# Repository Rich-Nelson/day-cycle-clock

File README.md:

# day-cycle-clock

This repository contains the mechanical and electrical CAD for the Day Cycle Clock.  The code can be found in this repo https://github.com/Rich-Nelson/day-cycle-clock-code

Links to the build video and blog post coming soon.

## CAD
Contains the mechanical models.  In the root directoy there is a .STEP and .SLDASM of the full assembly

- **STL** Has all of the printable files for the project
- **SLDPRT** Contains the individual component models and sub assemblies
- **SLDDRW** Contaisn the 2-D dimensioned drawings for some of the fabricated components, mainly the wooden enclosure
- **Backlight Bracket** 3 versions of the backlight screen assembly were made depending on which you want to use.
    - **v1** Backlight assembly with through hole 5mm LEDs
    - **v2** Backlight assembly with SMD LEDs on perf board
    - **v3** Backlight assembly with custom PCB (found int he PCB folder)

## PCB
Contains the KiCAD PCB files and Gerbers.

**Note** I may need to update some customer libraries into this repo so that the KiCAD project will load properly on other computers.  But for now the gerbers are available to make your own boards.

## Graphics
Contains the vector outlines used for the 3 cutout layers.

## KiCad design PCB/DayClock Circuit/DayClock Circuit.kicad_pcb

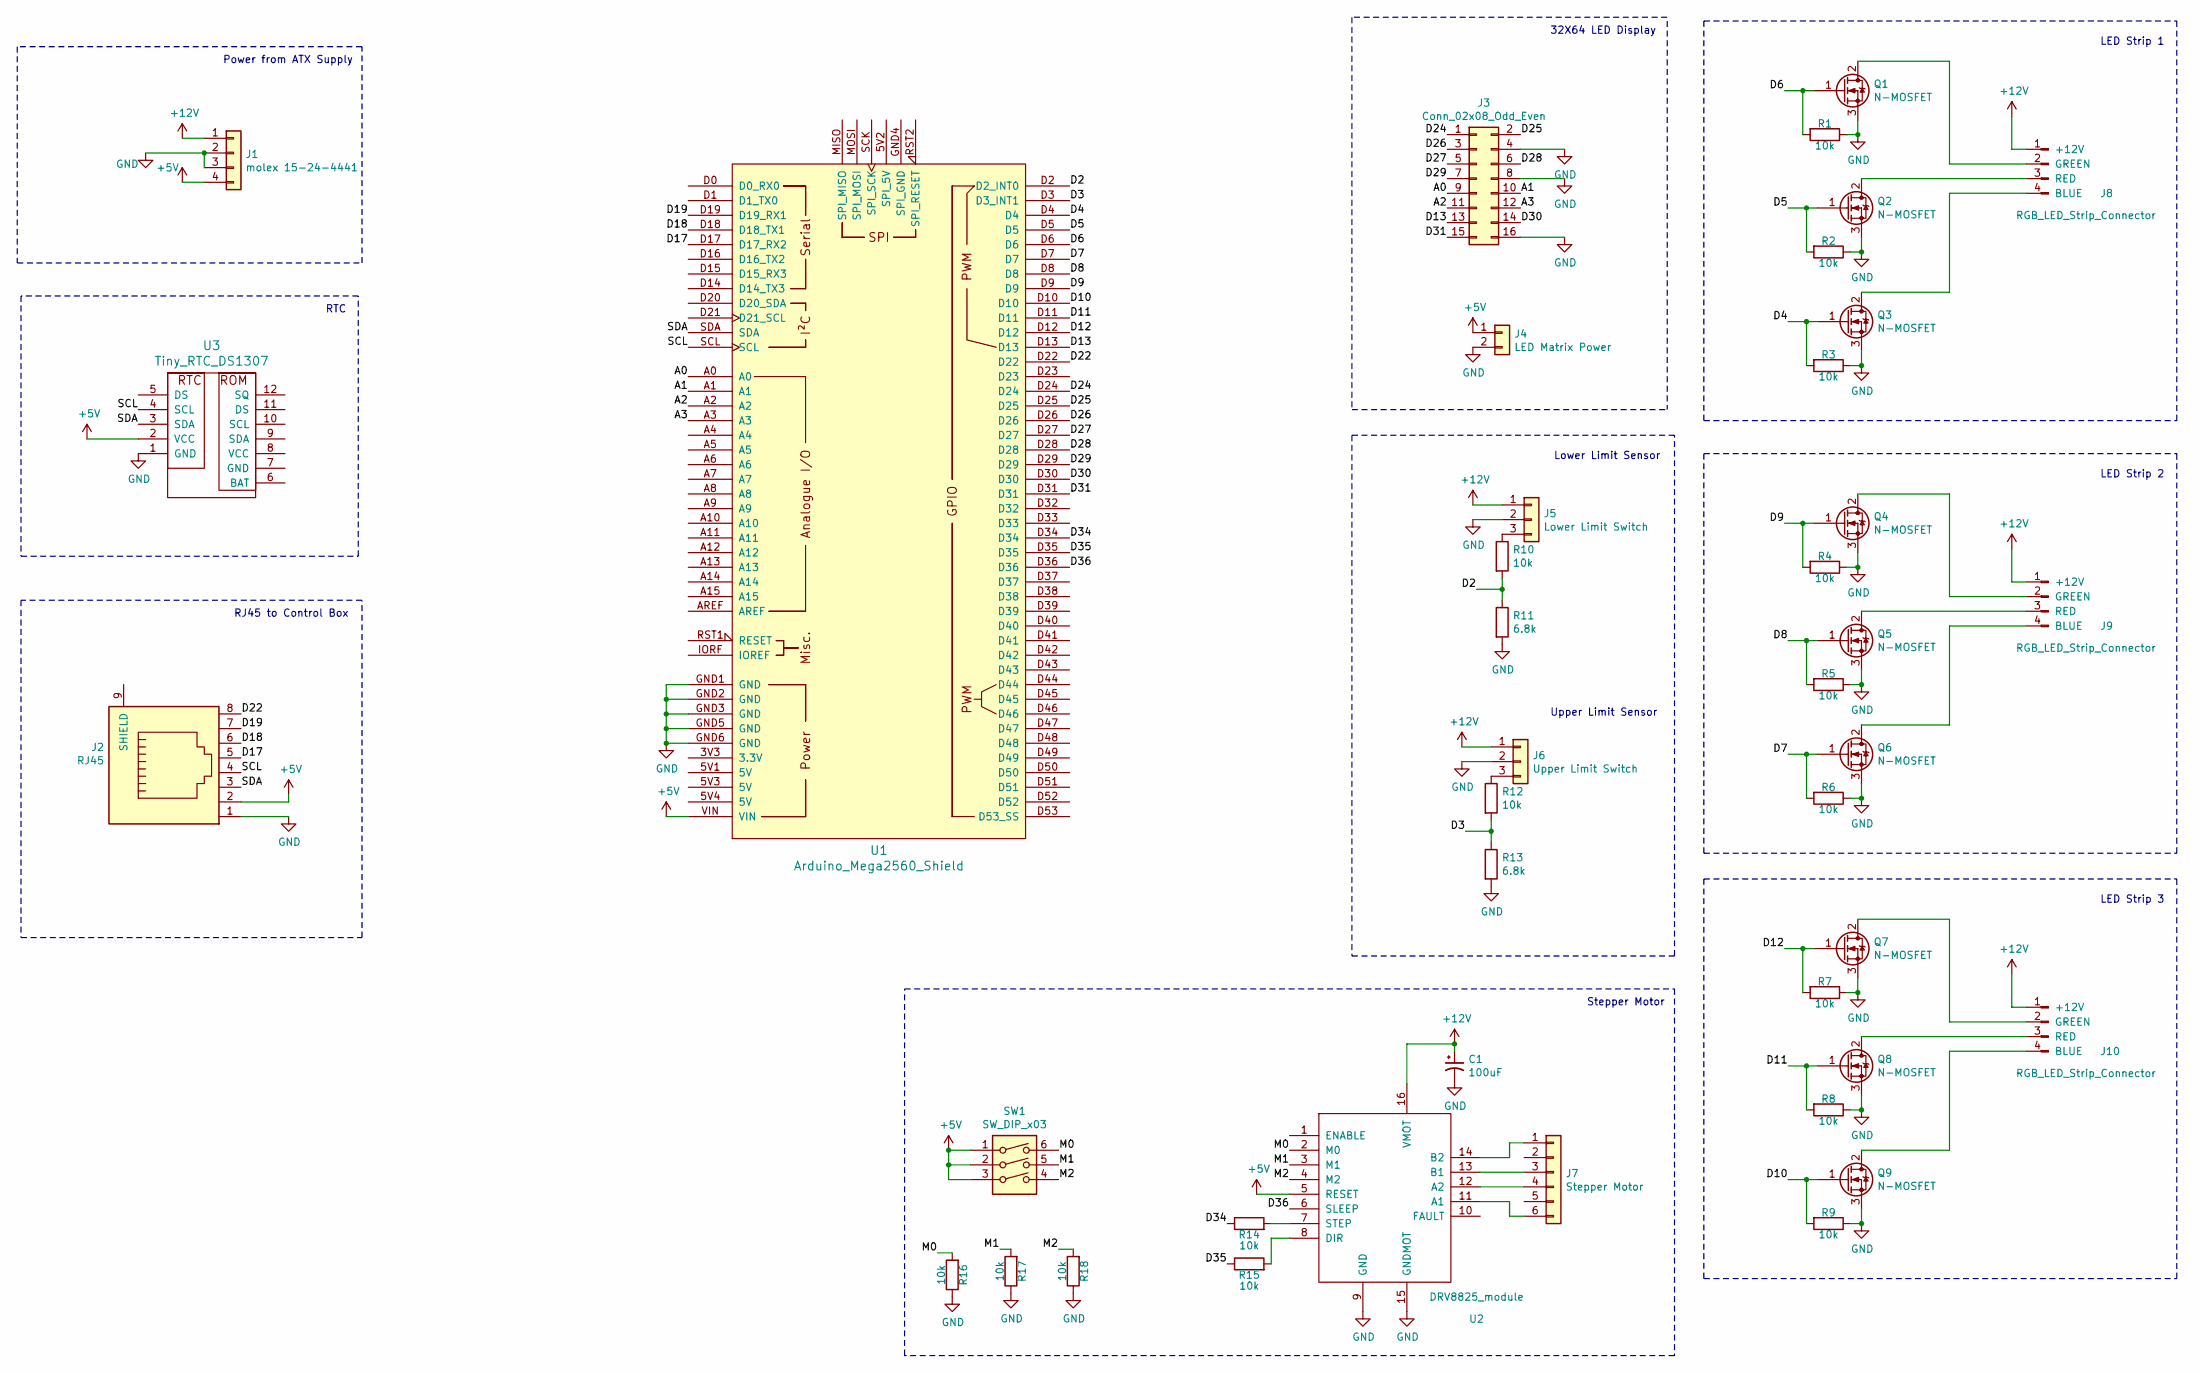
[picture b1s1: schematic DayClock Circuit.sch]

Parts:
C1: 100uF; CP_Radial_D6.3mm_P2.50mm
J1: molex 15-24-4441; Molex_15-24-4449_ATX_Power_Supply_Connector
J2: RJ45; RJ45_Amphenol_RJHSE538X
J3: Conn_02x08_Odd_Even; 3M_Header_2x8_Keyed
J4: LED Matrix Power; TerminalBlock_Altech_AK300-2_P5.00mm
J5: Lower Limit Switch; JST_XH_B03B-XH-A_1x03_P2.50mm_Vertical
J6: Upper Limit Switch; JST_XH_B03B-XH-A_1x03_P2.50mm_Vertical
J7: Stepper Motor; JST_XH_B06B-XH-A_1x06_P2.50mm_Vertical
J8, J9, J10: RGB_LED_Strip_Connector; JST_XH_B04B-XH-A_1x04_P2.50mm_Vertical
Q1, Q2, Q3, Q4, Q5, Q6, Q7, Q8, Q9: N-MOSFET; TO-251_IPAK_Vertical
R1, R2, R3, R4, R5, R6, R7, R8, R9, R10, R12, R14, R15, R16, R17, R18: 10k; R_0805_2012Metric_Pad1.15x1.50mm_HandSolder
R11, R13: 6.8k; R_0805_2012Metric_Pad1.15x1.50mm_HandSolder
SW1: SW_DIP_x03; SW_DIP_SPSTx03_Slide_6.7x9.18mm_W7.62mm_P2.54mm_LowProfile
U1: Arduino_Mega2560_Shield; Arduino_Mega2560_Shield_No_Serial_Header
U2: DRV8825_module; DRV8825_board
U3: Tiny_RTC_DS1307; TinyRTC-one-mounting-hole

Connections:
+5V: J1.4, J2.2, J4.1, SW1.1, SW1.2, SW1.3, U1.VIN, U2.5 (RESET), U3.2 (VCC)
+12V: C1.1, J1.1, J5.1, J6.1, J8.1 (+12V), J9.1 (+12V), J10.1 (+12V), U2.16 (VMOT); also elsewhere on the board
/5V3: U1.5V3 (5V); also elsewhere on the board
/A0: J3.9, U1.A0
/A1: J3.10, U1.A1
/A2: J3.11, U1.A2
/A3: J3.12, U1.A3
/D0: U1.D0 (D0_RX0); also elsewhere on the board
/D1: U1.D1 (D1_TX0); also elsewhere on the board
/D2: R10.2, R11.1, U1.D2 (D2_INT0)
/D3: R12.2, R13.1, U1.D3 (D3_INT1)
/D4: Q3.1 (G), R3.2, U1.D4
/D5: Q2.1 (G), R2.2, U1.D5
/D6: Q1.1 (G), R1.2, U1.D6
/D7: Q6.1 (G), R6.2, U1.D7
/D8: Q5.1 (G), R5.2, U1.D8
/D9: Q4.1 (G), R4.2, U1.D9
/D10: Q9.1 (G), R9.2, U1.D10
/D11: Q8.1 (G), R8.2, U1.D11
/D12: Q7.1 (G), R7.2, U1.D12
/D13: J3.13, U1.D13
/D14: U1.D14 (D14_TX3); also elsewhere on the board
/D15: U1.D15 (D15_RX3); also elsewhere on the board
/D16: U1.D16 (D16_TX2); also elsewhere on the board
/D17: J2.5, U1.D17 (D17_RX2)
/D18: J2.6, U1.D18 (D18_TX1)
/D19: J2.7, U1.D19 (D19_RX1)
/D20: U1.D20 (D20_SDA); also elsewhere on the board
/D21: U1.D21 (D21_SCL); also elsewhere on the board
/D22: J2.8, U1.D22
/D24: J3.1, U1.D24
/D25: J3.2, U1.D25
/D26: J3.3, U1.D26
/D27: J3.5, U1.D27
/D28: J3.6, U1.D28
/D29: J3.7, U1.D29
/D30: J3.14, U1.D30
/D31: J3.15, U1.D31
/D34: R14.1, U1.D34
/D35: R15.1, U1.D35
/D36: U1.D36, U2.6 (SLEEP)
/M0: R16.2, SW1.6, U2.2 (M0)
/M1: R17.2, SW1.5, U2.3 (M1)
/M2: R18.2, SW1.4, U2.4 (M2)
/SCL: J2.4, U1.SCL, U3.4 (SCL)
/SDA: J2.3, U1.SDA, U3.3 (SDA)
GND: C1.2, J1.2, J1.3, J2.1, J3.4, J3.8, J3.16, J4.2, J5.2, J6.2, Q1.3 (S), Q2.3 (S), Q3.3 (S), Q4.3 (S), Q5.3 (S), Q6.3 (S), Q7.3 (S), Q8.3 (S), Q9.3 (S), R1.1, R2.1, R3.1, R4.1, R5.1, R6.1, R7.1, R8.1, R9.1, R11.2, R13.2, R16.1, R17.1, R18.1, U1.GND1 (GND), U1.GND2 (GND), U1.GND3 (GND), U1.GND5 (GND), U1.GND6 (GND), U2.9 (GND), U2.15 (GNDMOT), U3.1 (GND); also elsewhere on the board
unnamed: J5.3, R10.1
unnamed: J6.3, R12.1
unnamed: J7.1, U2.14 (B2)
unnamed: J7.3, U2.13 (B1)
unnamed: J7.4, U2.12 (A2)
unnamed: J7.6, U2.11 (A1)
unnamed: J8.2 (GREEN), Q1.2 (D)
unnamed: J8.3 (RED), Q2.2 (D)
unnamed: J8.4 (BLUE), Q3.2 (D)
unnamed: J9.2 (GREEN), Q4.2 (D)
unnamed: J9.3 (RED), Q5.2 (D)
unnamed: J9.4 (BLUE), Q6.2 (D)
unnamed: J10.2 (GREEN), Q7.2 (D)
unnamed: J10.3 (RED), Q8.2 (D)
unnamed: J10.4 (BLUE), Q9.2 (D)
unnamed: R14.2, U2.7 (STEP)
unnamed: R15.2, U2.8 (DIR)

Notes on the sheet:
LED Strip 1
LED Strip 2
LED Strip 3
32X64 LED Display
RTC
Power from ATX Supply
Upper Limit Sensor
Lower Limit Sensor
Stepper Motor
RJ45 to Control Box

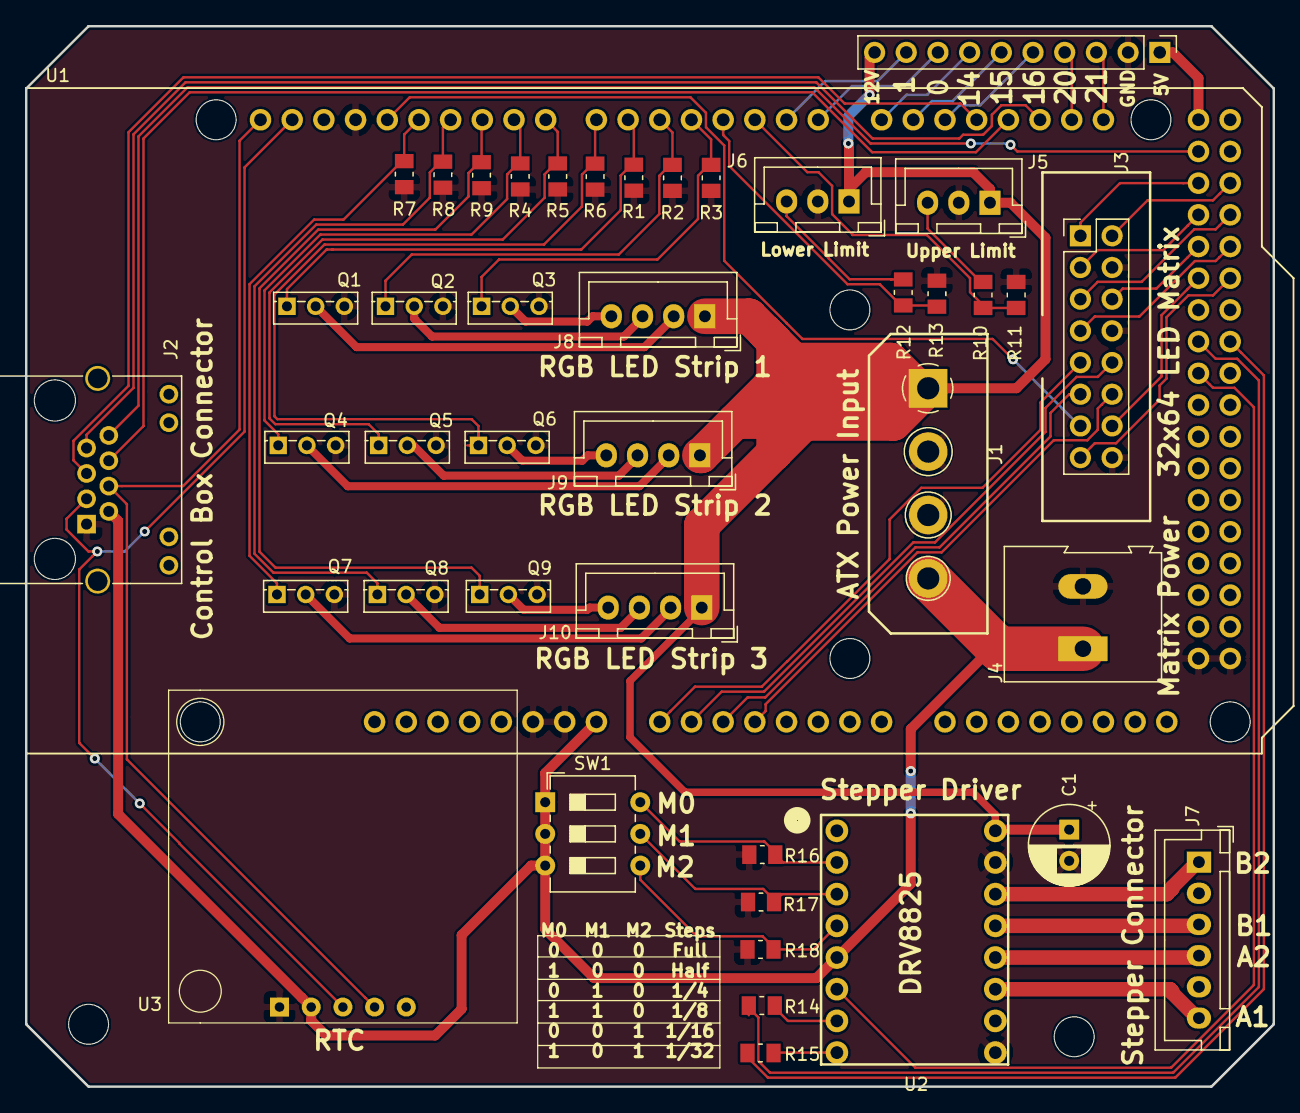
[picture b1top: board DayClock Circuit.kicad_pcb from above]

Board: 2 copper layers, 100.0 x 85.0 mm, 43 parts (0 on the bottom side), 64 nets.

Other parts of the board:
J11: Breakout Pins; PinHeader_1x10_P2.54mm_Vertical

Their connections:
+12V: J11.10; also elsewhere on the board
/5V3: J11.1; also elsewhere on the board
/D0: J11.8; also elsewhere on the board
/D1: J11.9; also elsewhere on the board
/D14: J11.7; also elsewhere on the board
/D15: J11.6; also elsewhere on the board
/D16: J11.5; also elsewhere on the board
/D20: J11.4; also elsewhere on the board
/D21: J11.3; also elsewhere on the board
GND: J11.2; also elsewhere on the board

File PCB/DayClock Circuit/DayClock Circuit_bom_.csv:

Component,Description,Part,References,Value,Footprint,Quantity Per PCB,Datasheet
1,Polarised capacitor,CP1_Small,C1,100uF,CP_Radial_D6.3mm_P2.50mm,1,
2,"Generic connector, single row, 01x10, script generated (kicad-library-utils/schlib/autogen/connector/)",Conn_01x10,J11,Breakout Pins,PinHeader_1x10_P2.54mm_Vertical,1,
3,"Generic connector, double row, 02x08, odd/even pin numbering scheme (row 1 odd numbers, row 2 even numbers), script generated (kicad-library-utils/schlib/autogen/connector/)",Conn_02x08_Odd_Even,J3,Conn_02x08_Odd_Even,3M_Header_2x8_Keyed,1,
4,"Generic connector, single row, 01x02, script generated (kicad-library-utils/schlib/autogen/connector/)",Conn_01x02,J4,LED Matrix Power,TerminalBlock_Altech_AK300-2_P5.00mm,1,
5,"Generic connector, single row, 01x03, script generated (kicad-library-utils/schlib/autogen/connector/)",Conn_01x03,J5,Lower Limit Switch,JST_XH_B03B-XH-A_1x03_P2.50mm_Vertical,1,
6,,RGB_LED_Strip_Connector,J8 J9 J10,RGB_LED_Strip_Connector,JST_XH_B04B-XH-A_1x04_P2.50mm_Vertical,3,
7,RJ45 connector with shield,RJ45,J2,RJ45,RJ45_Amphenol_RJHSE538X,1,
8,"Generic connector, single row, 01x06, script generated (kicad-library-utils/schlib/autogen/connector/)",Conn_01x06,J7,Stepper Motor,JST_XH_B06B-XH-A_1x06_P2.50mm_Vertical,1,
9,"Generic connector, single row, 01x03, script generated (kicad-library-utils/schlib/autogen/connector/)",Conn_01x03,J6,Upper Limit Switch,JST_XH_B03B-XH-A_1x03_P2.50mm_Vertical,1,
10,"Generic connector, single row, 01x04, script generated (kicad-library-utils/schlib/autogen/connector/)",Conn_01x04,J1,molex 15-24-4441,Molex_15-24-4449_ATX_Power_Supply_Connector,1,
11,"0.35A Id, 240V Vds, N-Channel MOSFET, SOT-223",BSP129,Q1 Q2 Q3 Q4 Q5 Q6 Q7 Q8 Q9,N-MOSFET,TO-251_IPAK_Vertical,9,https://www.infineon.com/dgdl/Infineon-BSP129-DS-v01_42-en.p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
12,Resistor,R,R1 R2 R3 R4 R5 R6 R7 R8 R9 R10 R12 R14 R15 R16 R17 R18,10k,R_0805_2012Metric_Pad1.15x1.50mm_HandSolder,16,
13,Resistor,R,R11 R13,6.8k,R_0805_2012Metric_Pad1.15x1.50mm_HandSolder,2,
14,"3x DIP Switch, Single Pole Single Throw (SPST) switch, small symbol",SW_DIP_x03,SW1,SW_DIP_x03,SW_DIP_SPSTx03_Slide_6.7x9.18mm_W7.62mm_P2.54mm_LowProfile,1,
15,Shield for Arduino Mega 2560,Arduino_Mega2560_Shield,U1,Arduino_Mega2560_Shield,Arduino_Mega2560_Shield_No_Serial_Header,1,https://store.arduino.cc/arduino-mega-2560-rev3
16,,DRV8825_module,U2,DRV8825_module,DRV8825_board,1,
17,,Tiny_RTC_DS1307,U3,Tiny_RTC_DS1307,TinyRTC-coin-side-up,1,





Component Groups:,17
Component Count:,43
Fitted Components:,43
Number of PCBs:,1
Total components:,43
Schematic Version:,
Schematic Date:,
BoM Date:,6/3/2018 11:47:07 PM
Schematic Source:,C:\Users\Rich\Dropbox\Projects\Skyline Shadowbox Day Cycle\day-cycle-clock\PCB\DayClock Circuit\DayClock Circuit.sch
KiCad Version:,Eeschema (5.0.0-rc2-dev-352-g017154715)

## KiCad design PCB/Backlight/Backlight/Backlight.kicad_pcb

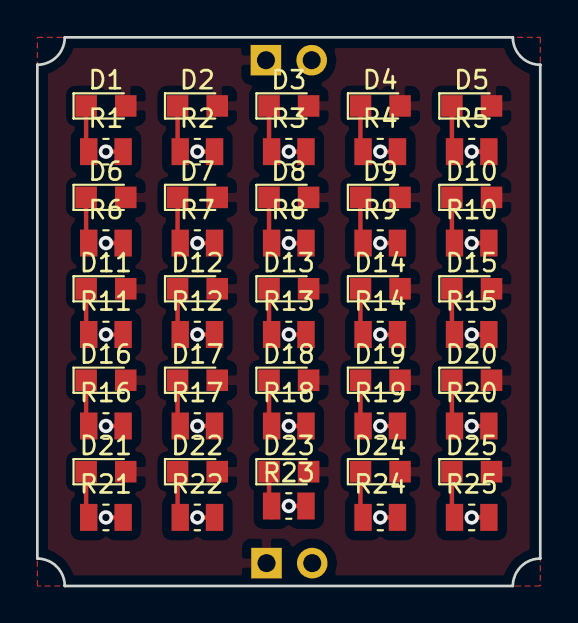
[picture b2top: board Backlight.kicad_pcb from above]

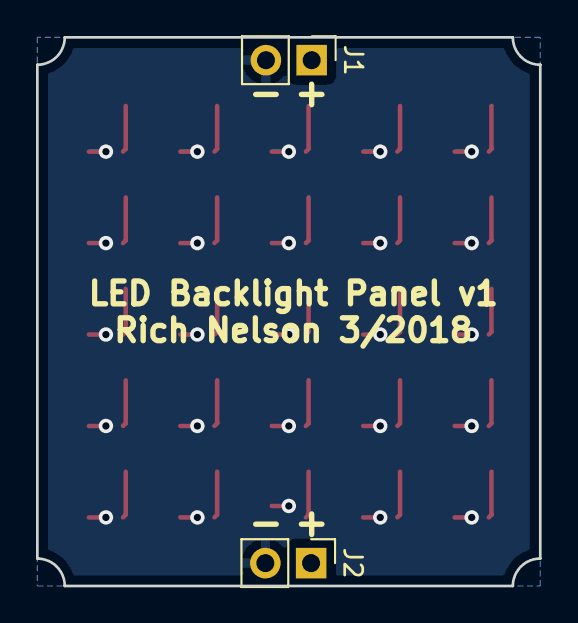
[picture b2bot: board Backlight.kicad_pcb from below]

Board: 2 copper layers, 27.9 x 30.5 mm, 52 parts (2 on the bottom side), 27 nets.

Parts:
D1, D2, D3, D4, D5, D6, D7, D8, D9, D10, D11, D12, D13, D14, D15, D16, D17, D18, D19, D20, D21, D22, D23, D24, D25: LED; LED_0805
J1, J2: Conn_01x02; PinHeader_1x02_P2.54mm_Vertical
R1, R2, R3, R4, R5, R6, R7, R8, R9, R10, R11, R12, R13, R14, R15, R16, R17, R18, R19, R20, R21, R22, R23, R24, R25: R; R_0805_2012Metric

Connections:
+5V: D1.2, D2.2, D3.2, D4.2, D5.2, D6.2, D7.2, D8.2, D9.2, D10.2, D11.2, D12.2, D13.2, D14.2, D15.2, D16.2, D17.2, D18.2, D19.2, D20.2, D21.2, D22.2, D23.2, D24.2, D25.2, J1.1, J2.1
GND: J1.2, J2.2, R1.2, R2.2, R3.2, R4.2, R5.2, R6.2, R7.2, R8.2, R9.2, R10.2, R11.2, R12.2, R13.2, R14.2, R15.2, R16.2, R17.2, R18.2, R19.2, R20.2, R21.2, R22.2, R23.2, R24.2, R25.2
unnamed: D1.1, R1.1
unnamed: D2.1, R2.1
unnamed: D3.1, R3.1
unnamed: D4.1, R4.1
unnamed: D5.1, R5.1
unnamed: D6.1, R6.1
unnamed: D7.1, R7.1
unnamed: D8.1, R8.1
unnamed: D9.1, R9.1
unnamed: D10.1, R10.1
unnamed: D11.1, R11.1
unnamed: D12.1, R12.1
unnamed: D13.1, R13.1
unnamed: D14.1, R14.1
unnamed: D15.1, R15.1
unnamed: D16.1, R16.1
unnamed: D17.1, R17.1
unnamed: D18.1, R18.1
unnamed: D19.1, R19.1
unnamed: D20.1, R20.1
unnamed: D21.1, R21.1
unnamed: D22.1, R22.1
unnamed: D23.1, R23.1
unnamed: D24.1, R24.1
unnamed: D25.1, R25.1

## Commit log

2018-05-16 Initial commit, day-cycle-clock rev 1
2018-05-19 Added support for altrnate TFT screen. there sems to be a huge numbr of 1.44 TFT screens on the marked with minor differences in dimensions and protocals.
2018-05-19 Added 2004 LCD screen connector to schematic
2018-05-22 Updated CAD for new TFT screen, and updated schamatic, adding the encoder.
2018-05-26 Updated Scheematic to inclide New RGB LED strips and i2c driver, and 32x64 matrix using an Arduino Uno
2018-05-30 Started moving components to the Arduino Mega, moved the 3 LED strips (9 PWM pins), and the 32x64 Matrix Display
2018-05-31 Added Power connecter. Moved RTC, Encoder, and 4002 LCD screen to the Arduino Mega. Lastly need to add stepper, CAT5 breakout for control box, and limit switches for the motor.
2018-06-01 Added Stepper with Driver and Proximity Sensor Limits
2018-06-01 Added resistors to steper sriver signal lines. This solved somem erratic behaviour of the stpper moving on it's own
2018-06-02 Split control box to a seperate PCB connected by a CAT5 cable. Schematic is complete, foot prints need to be finalized before layout.
2018-06-03 Added thick power traces and design rules.
2018-06-03 Started on signal wires
2018-06-04 Giant Day Cycle Clock Rev 1A sent to fab and components ordered
2018-06-18 Updated lots of CAD like the screen/motor belt drive. Also updated the graphics
2018-07-25 Final version for Maker Faire 2018
2018-10-07 Cleaned up directory
2018-10-09 Added README and added additional drawings
